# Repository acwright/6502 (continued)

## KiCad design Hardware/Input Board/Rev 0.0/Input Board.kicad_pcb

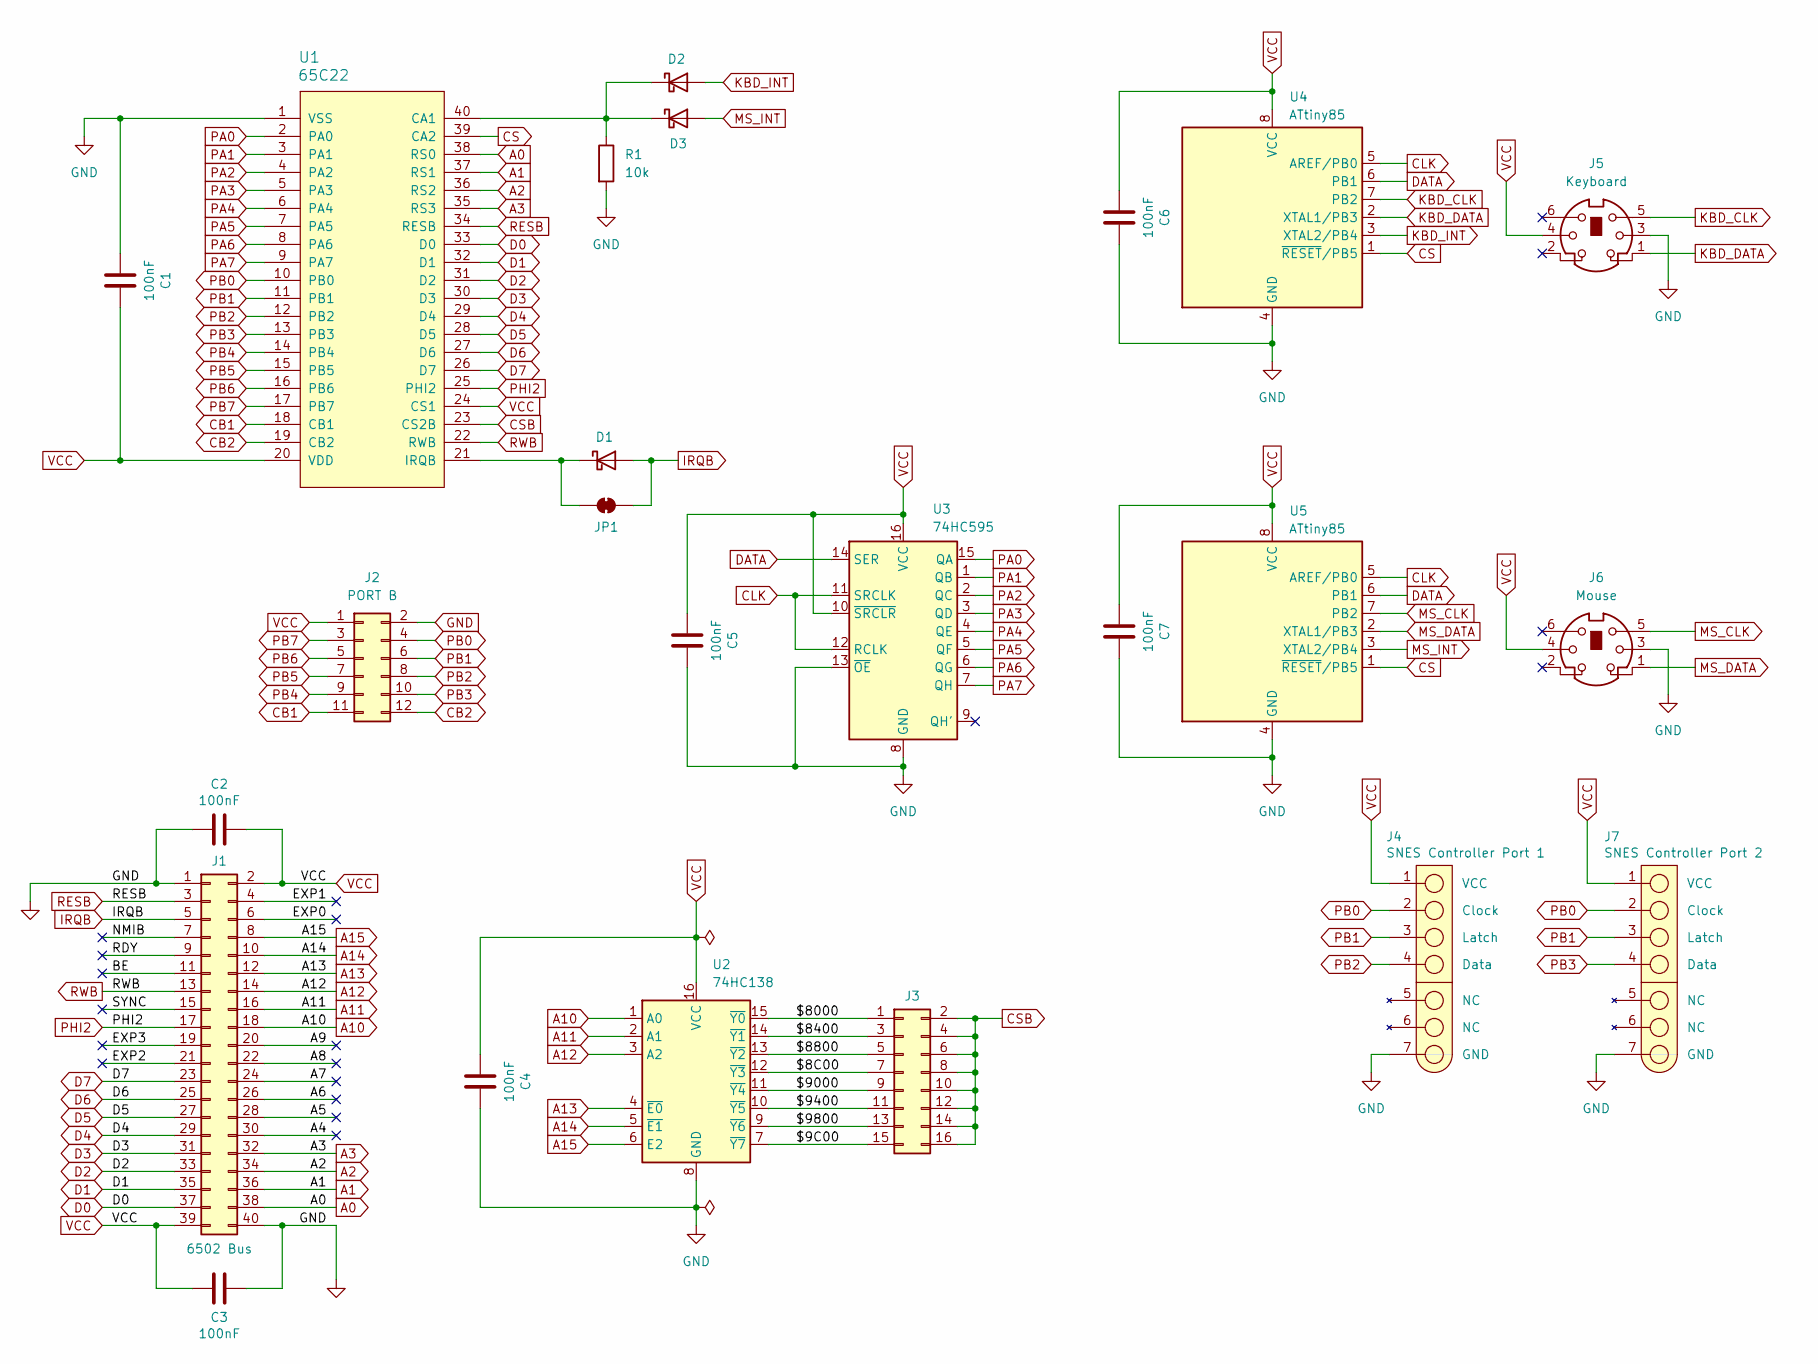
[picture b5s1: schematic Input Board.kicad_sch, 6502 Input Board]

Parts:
C1, C2, C3, C4, C5, C6, C7: 100nF; C_0805_2012Metric; LCSC C49678
D1, D2, D3: D_Schottky; D_DO-35_SOD27_P7.62mm_Horizontal
J1: 6502 Bus; 6502 Bus Connector
J2: PORT B; 6502 GPIO Connector
J3: Conn_02x08_Odd_Even; PinHeader_2x08_P2.54mm_Vertical
J4: SNES Controller Port 1; SNES Controller Port
J5: Keyboard; KMDGX-6S-BS
J6: Mouse; KMDGX-6S-BS
J7: SNES Controller Port 2; SNES Controller Port
JP1: SolderJumper_2_Bridged; SolderJumper-2_P1.3mm_Bridged_RoundedPad1.0x1.5mm
R1: 10k; R_0805_2012Metric; LCSC C17414
U1: 65C22; DIP-40_W15.24mm_Socket_LongPads
U2: 74HC138; SOIC-16_3.9x9.9mm_P1.27mm; LCSC C5602
U3: 74HC595; SOIC-16_3.9x9.9mm_P1.27mm; LCSC C5947
U4, U5: ATtiny85; DIP-8_W7.62mm_Socket_LongPads

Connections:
/$8C00: J3.7, U2.12 (~Y3)
/$9C00: J3.15, U2.7 (~Y7)
/$8000: J3.1, U2.15 (~Y0)
/$8400: J3.3, U2.14 (~Y1)
/$8800: J3.5, U2.13 (~Y2)
/$9000: J3.9, U2.11 (~Y4)
/$9400: J3.11, U2.10 (~Y5)
/$9800: J3.13, U2.9 (~Y6)
/A4: J1.30
/A5: J1.28
/A6: J1.26
/A7: J1.24
/A8: J1.22
/A9: J1.20
/BE: J1.11
/EXP0: J1.6
/EXP1: J1.4
/EXP2: J1.21
/EXP3: J1.19
/NMIB: J1.7
/RDY: J1.9
/SYNC: J1.15
A0: J1.38, U1.38 (RS0)
A1: J1.36, U1.37 (RS1)
A2: J1.34, U1.36 (RS2)
A3: J1.32, U1.35 (RS3)
A10: J1.18, U2.1 (A0)
A11: J1.16, U2.2 (A1)
A12: J1.14, U2.3 (A2)
A13: J1.12, U2.4 (~E0)
A14: J1.10, U2.5 (~E1)
A15: J1.8, U2.6 (E2)
CB1: J2.11, U1.18 (CB1)
CB2: J2.12, U1.19 (CB2)
CLK: U3.11 (SRCLK), U3.12 (RCLK), U4.5 (AREF/PB0), U5.5 (AREF/PB0)
CS: U1.39 (CA2), U4.1 (~RESET/PB5), U5.1 (~RESET/PB5)
CSB: J3.2, J3.4, J3.6, J3.8, J3.10, J3.12, J3.14, J3.16, U1.23 (CS2B)
D0: J1.37, U1.33 (D0)
D1: J1.35, U1.32 (D1)
D2: J1.33, U1.31 (D2)
D3: J1.31, U1.30 (D3)
D4: J1.29, U1.29 (D4)
D5: J1.27, U1.28 (D5)
D6: J1.25, U1.27 (D6)
D7: J1.23, U1.26 (D7)
DATA: U3.14 (SER), U4.6 (PB1), U5.6 (PB1)
GND: C1.1, C2.2, C3.1, C4.2, C5.2, C6.2, C7.2, J1.1, J1.40, J2.2, J4.7 (GND), J5.3, J6.3, J7.7 (GND), R1.2, U1.1 (VSS), U2.8 (GND), U3.8 (GND), U3.13 (~OE), U4.4 (GND), U5.4 (GND)
IRQB: D1.2 (A), J1.5, JP1.2 (B)
KBD_CLK: J5.5, U4.7 (PB2)
KBD_DATA: J5.1, U4.2 (XTAL1/PB3)
KBD_INT: D2.2 (A), U4.3 (XTAL2/PB4)
MS_CLK: J6.5, U5.7 (PB2)
MS_DATA: J6.1, U5.2 (XTAL1/PB3)
MS_INT: D3.2 (A), U5.3 (XTAL2/PB4)
unnamed: D1.1 (K), JP1.1 (A), U1.21 (IRQB)
unnamed: D2.1 (K), D3.1 (K), R1.1, U1.40 (CA1)
PA0: U1.2 (PA0), U3.15 (QA)
PA1: U1.3 (PA1), U3.1 (QB)
PA2: U1.4 (PA2), U3.2 (QC)
PA3: U1.5 (PA3), U3.3 (QD)
PA4: U1.6 (PA4), U3.4 (QE)
PA5: U1.7 (PA5), U3.5 (QF)
PA6: U1.8 (PA6), U3.6 (QG)
PA7: U1.9 (PA7), U3.7 (QH)
PB0: J2.4, J4.2 (Clock), J7.2 (Clock), U1.10 (PB0)
PB1: J2.6, J4.3 (Latch), J7.3 (Latch), U1.11 (PB1)
PB2: J2.8, J4.4 (Data), U1.12 (PB2)
PB3: J2.10, J7.4 (Data), U1.13 (PB3)
PB4: J2.9, U1.14 (PB4)
PB5: J2.7, U1.15 (PB5)
PB6: J2.5, U1.16 (PB6)
PB7: J2.3, U1.17 (PB7)
PHI2: J1.17, U1.25 (PHI2)
RESB: J1.3, U1.34 (RESB)
RWB: J1.13, U1.22 (RWB)
VCC: C1.2, C2.1, C3.2, C4.1, C5.1, C6.1, C7.1, J1.2, J1.39, J2.1, J4.1 (VCC), J5.4, J6.4, J7.1 (VCC), U1.20 (VDD), U1.24 (CS1), U2.16 (VCC), U3.10 (~SRCLR), U3.16 (VCC), U4.8 (VCC), U5.8 (VCC)

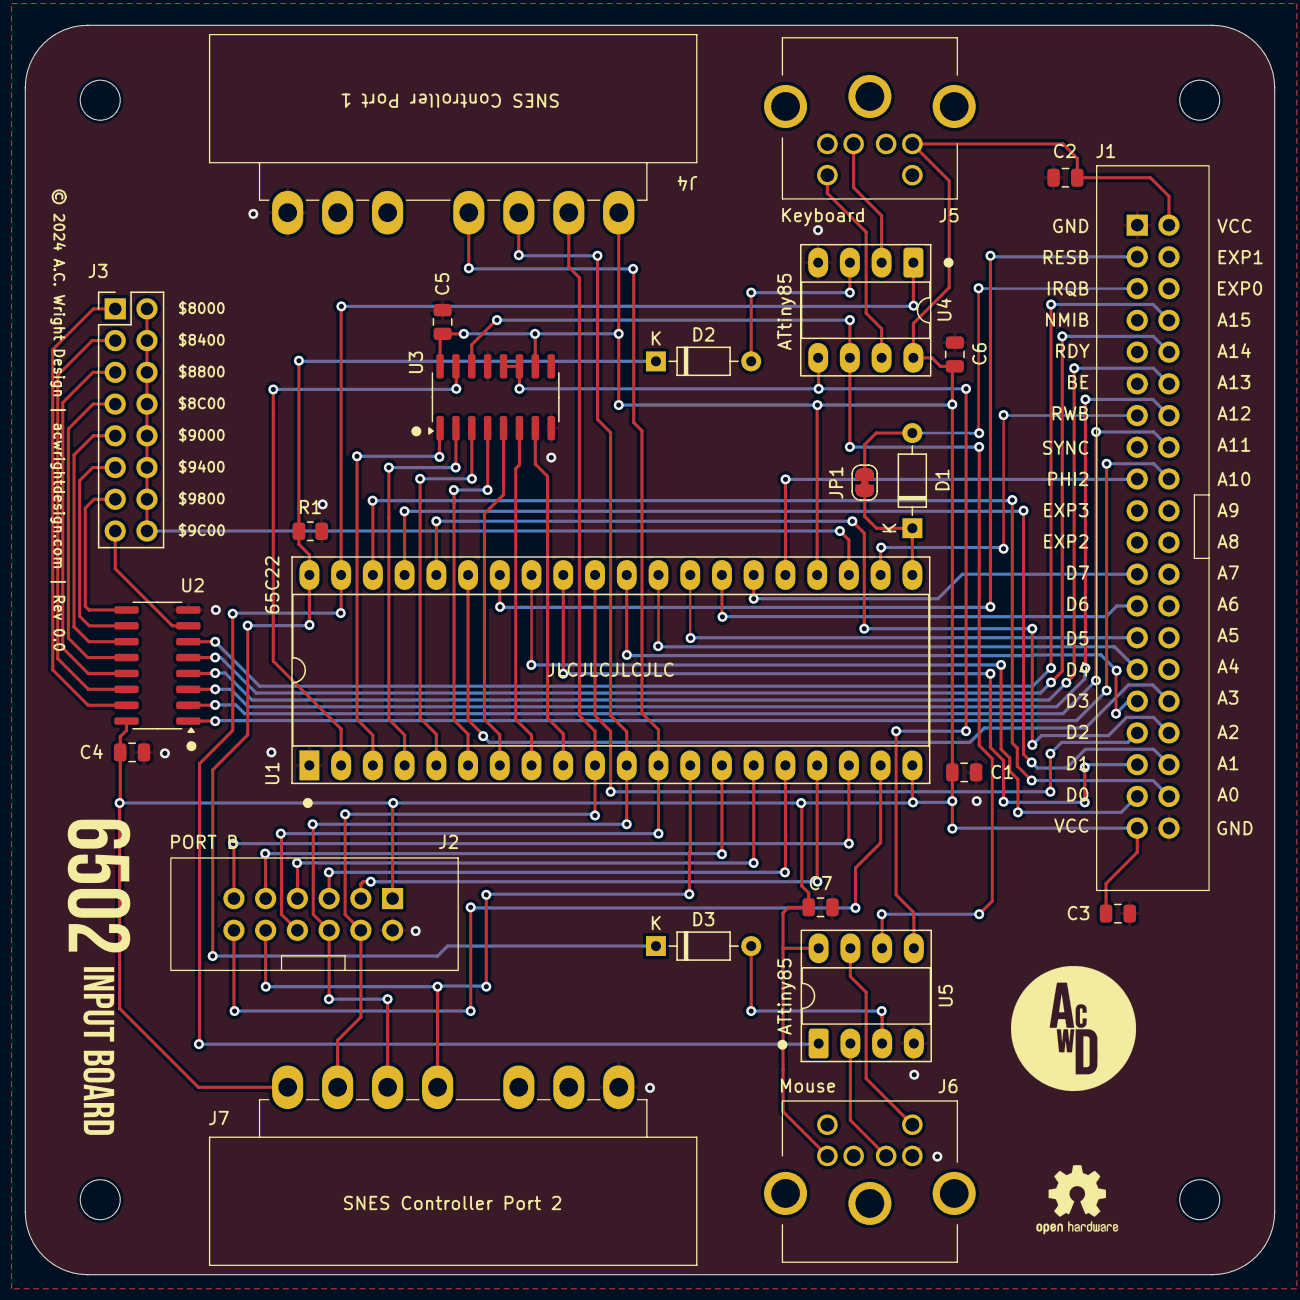
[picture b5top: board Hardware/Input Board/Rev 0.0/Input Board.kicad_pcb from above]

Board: 2 copper layers, 100.0 x 100.0 mm, 28 parts (0 on the bottom side), 62 nets.

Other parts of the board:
H1, H2, H3, H4: MountingHole; MountingHole_3.2mm_M3

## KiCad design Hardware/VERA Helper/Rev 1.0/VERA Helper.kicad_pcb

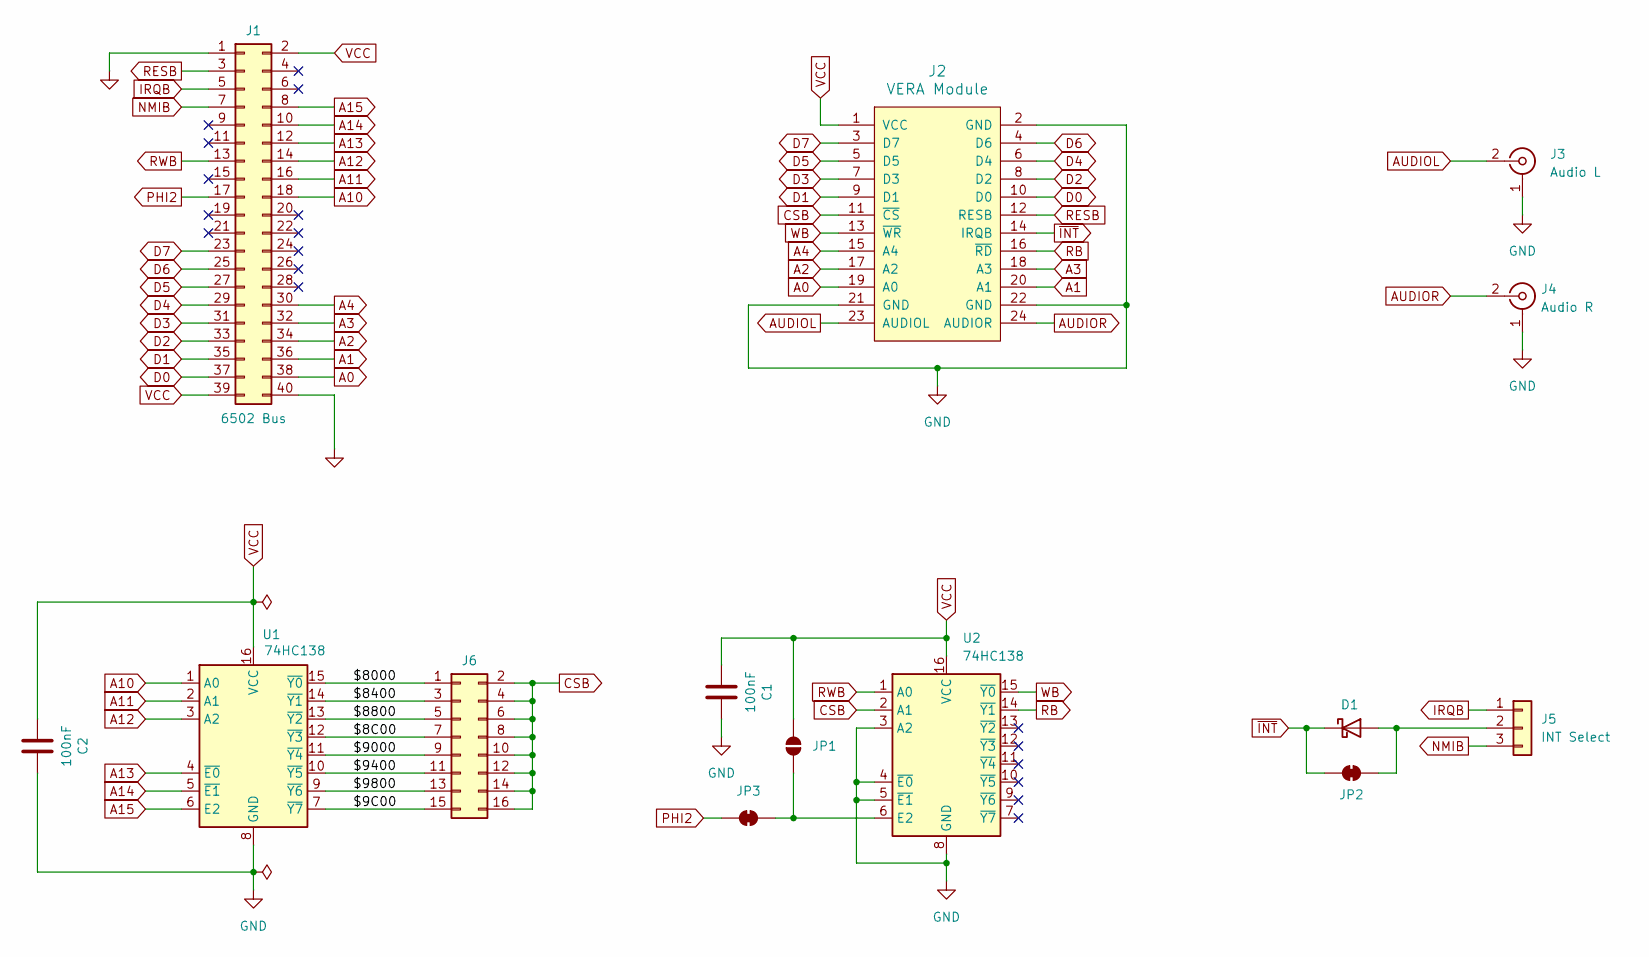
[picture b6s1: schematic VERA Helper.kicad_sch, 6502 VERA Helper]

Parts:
C1, C2: 100nF; C_Disc_D5.0mm_W2.5mm_P5.00mm; LCSC C49678
D1: D_Schottky; D_DO-35_SOD27_P7.62mm_Horizontal
J1: 6502 Bus; 6502 Bus Connector
J2: VERA Module; PinHeader_2x12_P2.54mm_Vertical
J3: Audio L; SWITCHCRAFT_PJRAN1X1U02X
J4: Audio R; SWITCHCRAFT_PJRAN1X1U02X
J5: INT Select; PinHeader_1x03_P2.54mm_Vertical
J6: Conn_02x08_Odd_Even; PinHeader_2x08_P2.54mm_Vertical
JP1: SolderJumper_2_Open; SolderJumper-2_P1.3mm_Open_RoundedPad1.0x1.5mm
JP2, JP3: SolderJumper_2_Bridged; SolderJumper-2_P1.3mm_Bridged_RoundedPad1.0x1.5mm
U1, U2: 74HC138; DIP-16_W7.62mm_Socket_LongPads; LCSC C5602

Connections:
/$8C00: J6.7, U1.12 (~Y3)
/$9C00: J6.15, U1.7 (~Y7)
/$8000: J6.1, U1.15 (~Y0)
/$8400: J6.3, U1.14 (~Y1)
/$8800: J6.5, U1.13 (~Y2)
/$9000: J6.9, U1.11 (~Y4)
/$9400: J6.11, U1.10 (~Y5)
/$9800: J6.13, U1.9 (~Y6)
A0: J1.38, J2.19 (A0)
A1: J1.36, J2.20 (A1)
A2: J1.34, J2.17 (A2)
A3: J1.32, J2.18 (A3)
A4: J1.30, J2.15 (A4)
A10: J1.18, U1.1 (A0)
A11: J1.16, U1.2 (A1)
A12: J1.14, U1.3 (A2)
A13: J1.12, U1.4 (~E0)
A14: J1.10, U1.5 (~E1)
A15: J1.8, U1.6 (E2)
AUDIOL: J2.23 (AUDIOL), J3.2 (In)
AUDIOR: J2.24 (AUDIOR), J4.2 (In)
CSB: J2.11 (~CS), J6.2, J6.4, J6.6, J6.8, J6.10, J6.12, J6.14, J6.16, U2.2 (A1)
D0: J1.37, J2.10 (D0)
D1: J1.35, J2.9 (D1)
D2: J1.33, J2.8 (D2)
D3: J1.31, J2.7 (D3)
D4: J1.29, J2.6 (D4)
D5: J1.27, J2.5 (D5)
D6: J1.25, J2.4 (D6)
D7: J1.23, J2.3 (D7)
GND: C1.2, C2.2, J1.1, J1.40, J2.2 (GND), J2.21 (GND), J2.22 (GND), J3.1 (Ext), J4.1 (Ext), U1.8 (GND), U2.3 (A2), U2.4 (~E0), U2.5 (~E1), U2.8 (GND)
IRQB: J1.5, J5.1
NMIB: J1.7, J5.3
unnamed: D1.2 (A), J5.2, JP2.2 (B)
unnamed: JP1.2 (B), JP3.1 (A), U2.6 (E2)
PHI2: J1.17, JP3.2 (B)
RB: J2.16 (~RD), U2.14 (~Y1)
RESB: J1.3, J2.12 (RESB)
RWB: J1.13, U2.1 (A0)
VCC: C1.1, C2.1, J1.2, J1.39, J2.1 (VCC), JP1.1 (A), U1.16 (VCC), U2.16 (VCC)
WB: J2.13 (~WR), U2.15 (~Y0)
~INT: D1.1 (K), J2.14 (IRQB), JP2.1 (A)

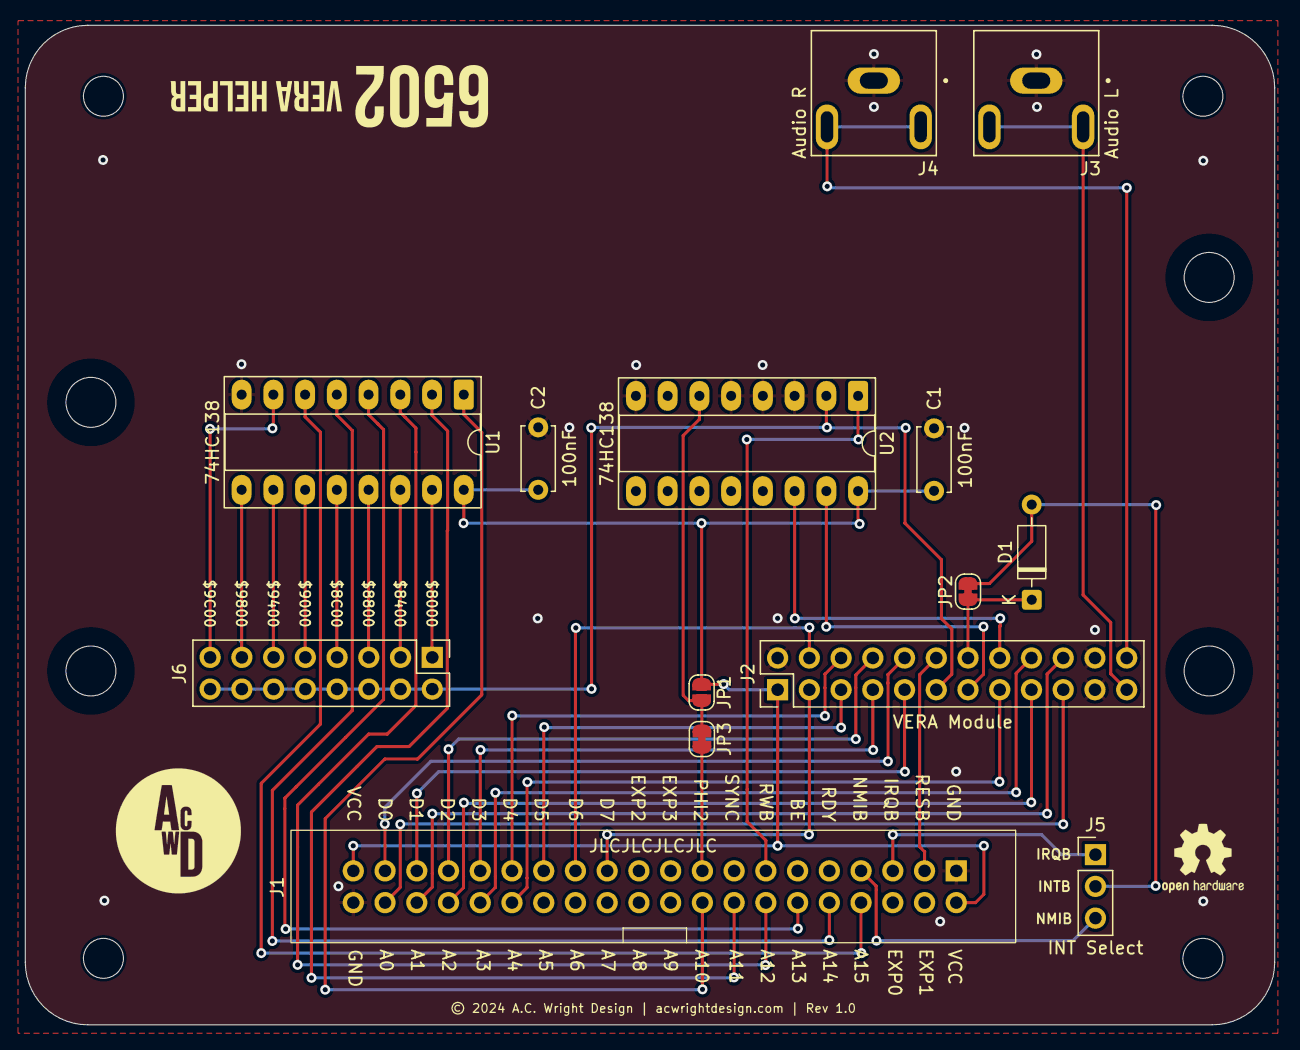
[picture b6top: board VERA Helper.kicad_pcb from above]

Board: 2 copper layers, 100.0 x 80.0 mm, 18 parts (0 on the bottom side), 42 nets.

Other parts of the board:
H1, H2, H3, H4: MountingHole; MountingHole_3.2mm_M3

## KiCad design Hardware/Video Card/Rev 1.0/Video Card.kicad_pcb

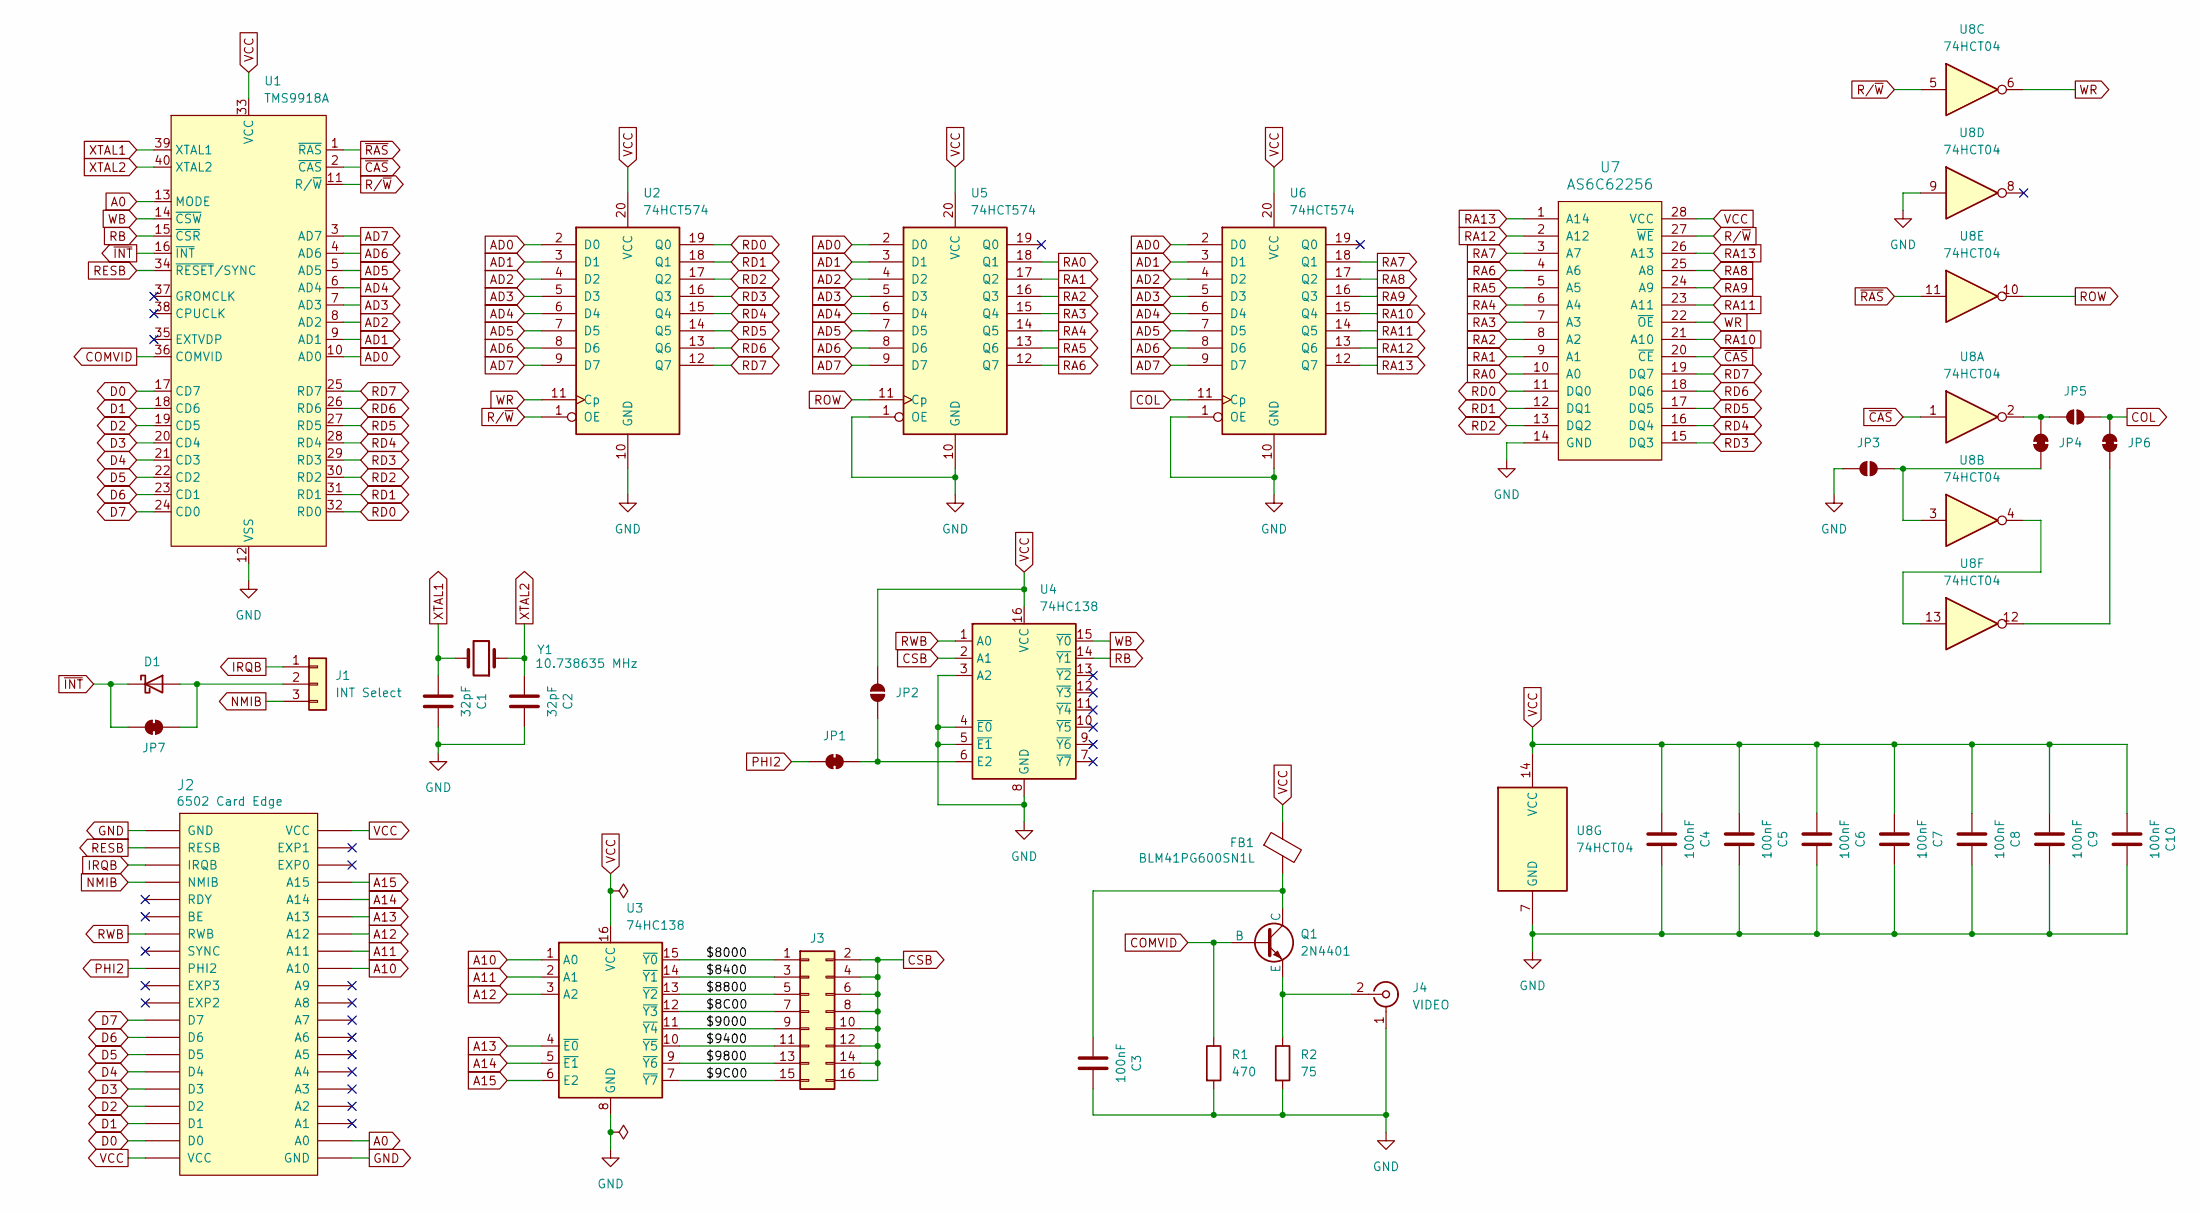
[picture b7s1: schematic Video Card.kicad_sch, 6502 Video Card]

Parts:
C1, C2: 32pF; C_Disc_D5.0mm_W2.5mm_P2.50mm; LCSC C107114
C3, C4, C5, C6, C7, C8, C9, C10: 100nF; C_0805_2012Metric; LCSC C49678
D1: D_Schottky; D_DO-35_SOD27_P7.62mm_Horizontal
FB1: BLM41PG600SN1L; L_1806_4516Metric; LCSC C85844
J1: INT Select; PinHeader_1x03_P2.54mm_Vertical
J2: 6502 Card Edge
J3: Conn_02x08_Odd_Even; PinHeader_2x08_P2.54mm_Vertical
J4: VIDEO; SWITCHCRAFT_PJRAN1X1U04X
JP1, JP4, JP6, JP7: SolderJumper_2_Bridged; SolderJumper-2_P1.3mm_Bridged_RoundedPad1.0x1.5mm
JP2, JP3, JP5: SolderJumper_2_Open; SolderJumper-2_P1.3mm_Open_RoundedPad1.0x1.5mm
Q1: 2N4401; TO-92_HandSolder
R1: 470; R_0805_2012Metric; LCSC C17710
R2: 75; R_0805_2012Metric; LCSC C17820
U1: TMS9918A; DIP-40_W15.24mm_Socket_LongPads
U2, U5, U6: 74HCT574; SOIC-20W_7.5x12.8mm_P1.27mm; LCSC C6001
U3, U4: 74HC138; SOIC-16_3.9x9.9mm_P1.27mm; LCSC C5602
U7: AS6C62256; DIP-28_W15.24mm_Socket_LongPads
U8: 74HCT04; SO-14_3.9x8.65mm_P1.27mm; LCSC C672096
Y1: 10.738635 MHz; Crystal_HC49-U_Vertical; Mouser 774-MP107-E

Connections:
/$8C00: J3.7, U3.12 (~Y3)
/$9C00: J3.15, U3.7 (~Y7)
/$8000: J3.1, U3.15 (~Y0)
/$8400: J3.3, U3.14 (~Y1)
/$8800: J3.5, U3.13 (~Y2)
/$9000: J3.9, U3.11 (~Y4)
/$9400: J3.11, U3.10 (~Y5)
/$9800: J3.13, U3.9 (~Y6)
A0: J2.A0, U1.13 (MODE)
A10: J2.A10, U3.1 (A0)
A11: J2.A11, U3.2 (A1)
A12: J2.A12, U3.3 (A2)
A13: J2.A13, U3.4 (~E0)
A14: J2.A14, U3.5 (~E1)
A15: J2.A15, U3.6 (E2)
AD0: U1.10 (AD0), U2.2 (D0), U5.2 (D0), U6.2 (D0)
AD1: U1.9 (AD1), U2.3 (D1), U5.3 (D1), U6.3 (D1)
AD2: U1.8 (AD2), U2.4 (D2), U5.4 (D2), U6.4 (D2)
AD3: U1.7 (AD3), U2.5 (D3), U5.5 (D3), U6.5 (D3)
AD4: U1.6 (AD4), U2.6 (D4), U5.6 (D4), U6.6 (D4)
AD5: U1.5 (AD5), U2.7 (D5), U5.7 (D5), U6.7 (D5)
AD6: U1.4 (AD6), U2.8 (D6), U5.8 (D6), U6.8 (D6)
AD7: U1.3 (AD7), U2.9 (D7), U5.9 (D7), U6.9 (D7)
COL: JP5.1 (A), JP6.2 (B), U6.11 (Cp)
COMVID: Q1.2 (B), R1.1, U1.36 (COMVID)
CSB: J3.2, J3.4, J3.6, J3.8, J3.10, J3.12, J3.14, J3.16, U4.2 (A1)
D0: J2.D0, U1.17 (CD7)
D1: J2.D1, U1.18 (CD6)
D2: J2.D2, U1.19 (CD5)
D3: J2.D3, U1.20 (CD4)
D4: J2.D4, U1.21 (CD3)
D5: J2.D5, U1.22 (CD2)
D6: J2.D6, U1.23 (CD1)
D7: J2.D7, U1.24 (CD0)
GND: C1.2, C2.2, C3.2, C4.2, C5.2, C6.2, C7.2, C8.2, C9.2, C10.2, J2.GND, J4.1 (Ext), JP3.2 (B), R1.2, R2.2, U1.12 (VSS), U2.10 (GND), U3.8 (GND), U4.3 (A2), U4.4 (~E0), U4.5 (~E1), U4.8 (GND), U5.1 (OE), U5.10 (GND), U6.1 (OE), U6.10 (GND), U7.14 (GND), U8.7 (GND), U8.9
IRQB: J1.1, J2.IRQB
NMIB: J1.3, J2.NMIB
unnamed: D1.2 (A), J1.2, JP7.2 (B)
unnamed: J4.2 (In), Q1.3 (E), R2.1
unnamed: JP1.1 (A), JP2.2 (B), U4.6 (E2)
unnamed: JP3.1 (A), JP4.1 (A), U8.3
unnamed: JP4.2 (B), JP5.2 (B), U8.2
unnamed: JP6.1 (A), U8.12
unnamed: C3.1, FB1.2, Q1.1 (C)
unnamed: U8.4, U8.13
PHI2: J2.PHI2, JP1.2 (B)
RA0: U5.18 (Q1), U7.10 (A0)
RA1: U5.17 (Q2), U7.9 (A1)
RA2: U5.16 (Q3), U7.8 (A2)
RA3: U5.15 (Q4), U7.7 (A3)
RA4: U5.14 (Q5), U7.6 (A4)
RA5: U5.13 (Q6), U7.5 (A5)
RA6: U5.12 (Q7), U7.4 (A6)
RA7: U6.18 (Q1), U7.3 (A7)
RA8: U6.17 (Q2), U7.25 (A8)
RA9: U6.16 (Q3), U7.24 (A9)
RA10: U6.15 (Q4), U7.21 (A10)
RA11: U6.14 (Q5), U7.23 (A11)
RA12: U6.13 (Q6), U7.2 (A12)
RA13: U6.12 (Q7), U7.1 (A14), U7.26 (A13)
RB: U1.15 (~CSR), U4.14 (~Y1)
RD0: U1.32 (RD0), U2.19 (Q0), U7.11 (DQ0)
RD1: U1.31 (RD1), U2.18 (Q1), U7.12 (DQ1)
RD2: U1.30 (RD2), U2.17 (Q2), U7.13 (DQ2)
RD3: U1.29 (RD3), U2.16 (Q3), U7.15 (DQ3)
RD4: U1.28 (RD4), U2.15 (Q4), U7.16 (DQ4)
RD5: U1.27 (RD5), U2.14 (Q5), U7.17 (DQ5)
RD6: U1.26 (RD6), U2.13 (Q6), U7.18 (DQ6)
RD7: U1.25 (RD7), U2.12 (Q7), U7.19 (DQ7)
RESB: J2.RESB, U1.34 (~RESET/SYNC)
ROW: U5.11 (Cp), U8.10
RWB: J2.RWB, U4.1 (A0)
R/~W: U1.11 (R/~W), U2.1 (OE), U7.27 (~WE), U8.5
VCC: C4.1, C5.1, C6.1, C7.1, C8.1, C9.1, C10.1, FB1.1, J2.VCC, JP2.1 (A), U1.33 (VCC), U2.20 (VCC), U3.16 (VCC), U4.16 (VCC), U5.20 (VCC), U6.20 (VCC), U7.28 (VCC), U8.14 (VCC)
WB: U1.14 (~CSW), U4.15 (~Y0)
WR: U2.11 (Cp), U7.22 (~OE), U8.6
XTAL1: C1.1, U1.39 (XTAL1), Y1.2
XTAL2: C2.1, U1.40 (XTAL2), Y1.1
~CAS: U1.2 (~CAS), U7.20 (~CE), U8.1
~INT: D1.1 (K), JP7.1 (A), U1.16 (~INT)
~RAS: U1.1 (~RAS), U8.11

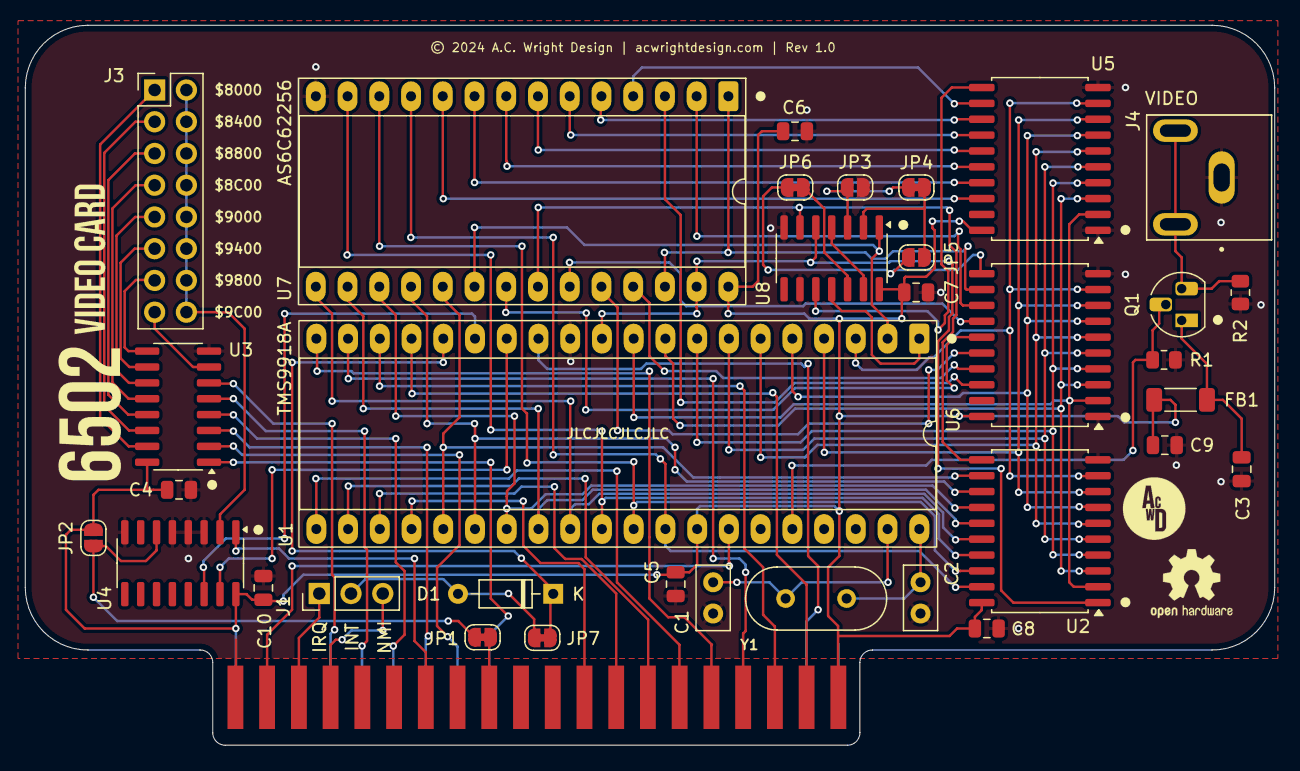
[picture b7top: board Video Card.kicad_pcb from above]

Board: 2 copper layers, 100.0 x 57.6 mm, 35 parts (0 on the bottom side), 81 nets.

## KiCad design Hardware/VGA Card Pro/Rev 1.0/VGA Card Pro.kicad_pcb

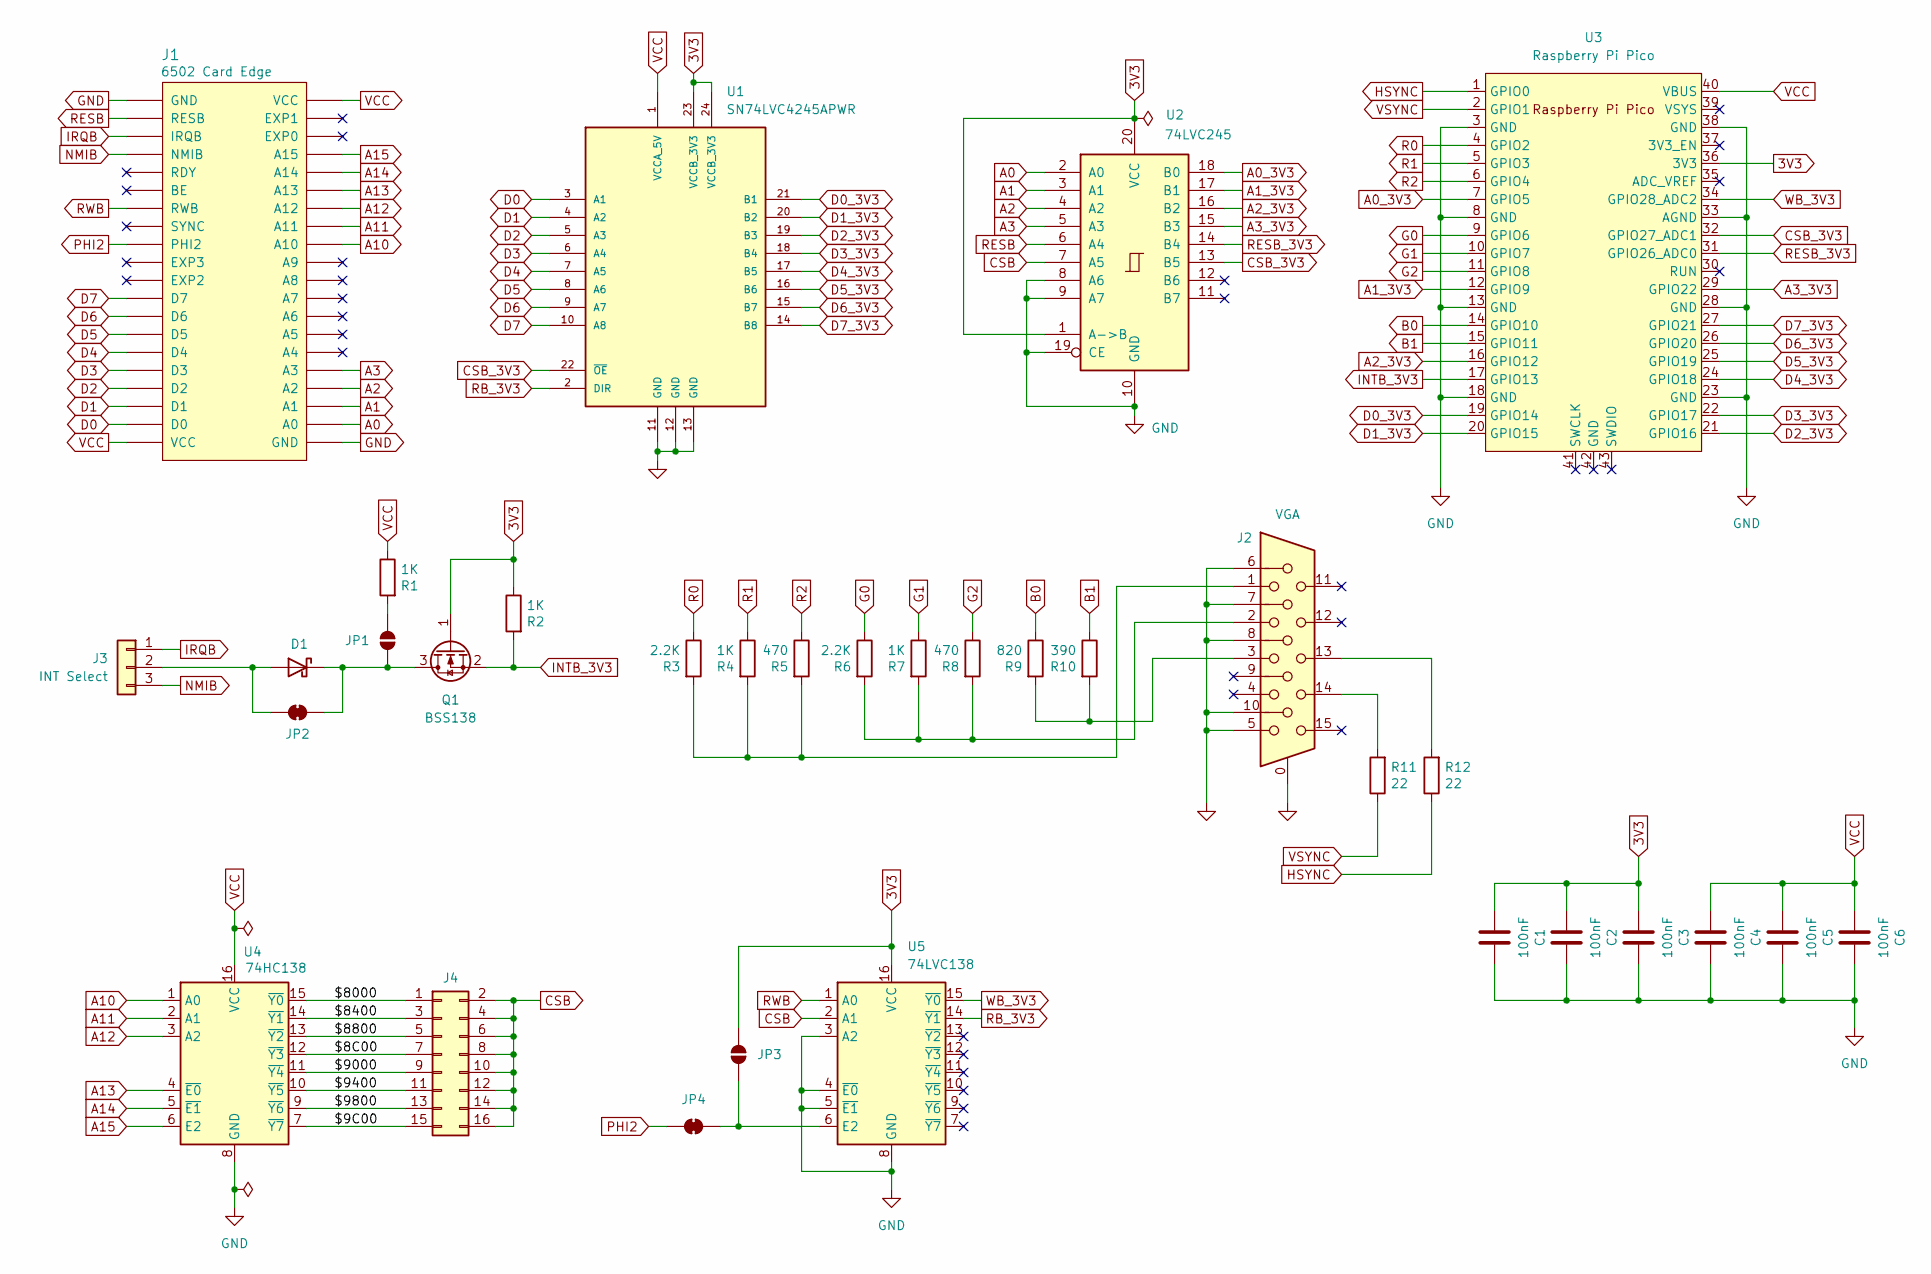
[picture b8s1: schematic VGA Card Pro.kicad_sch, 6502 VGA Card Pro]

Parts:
C1, C2, C3, C4, C5, C6: 100nF; C_0805_2012Metric; LCSC C49678
D1: D_Schottky; D_DO-35_SOD27_P7.62mm_Horizontal
J1: 6502 Card Edge
J2: VGA; DSUB-15-HD_Socket_Horizontal_P2.29x1.90mm_EdgePinOffset3.03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
J3: INT Select; PinHeader_1x03_P2.54mm_Vertical
J4: Conn_02x08_Odd_Even; PinHeader_2x08_P2.54mm_Vertical
JP1, JP3: SolderJumper_2_Open; SolderJumper-2_P1.3mm_Open_RoundedPad1.0x1.5mm
JP2, JP4: SolderJumper_2_Bridged; SolderJumper-2_P1.3mm_Bridged_RoundedPad1.0x1.5mm
Q1: BSS138; SOT-23; LCSC C78284
R1, R2, R4, R7: 1K; R_0805_2012Metric; LCSC C17513
R3, R6: 2.2K; R_0805_2012Metric; LCSC C17520
R5, R8: 470; R_0805_2012Metric; LCSC C17710
R9: 820; R_0805_2012Metric; LCSC C17837
R10: 390; R_0805_2012Metric; LCSC C17655
R11, R12: 22; R_0805_2012Metric; LCSC C17561
U1: SN74LVC4245APWR; TSSOP-24_4.4x7.8mm_P0.65mm; LCSC C7859
U2: 74LVC245; TSSOP-20_4.4x6.5mm_P0.65mm; LCSC C6082
U3: Raspberry Pi Pico
U4: 74HC138; SOIC-16_3.9x9.9mm_P1.27mm; LCSC C5602
U5: 74LVC138; SOIC-16_3.9x9.9mm_P1.27mm; LCSC C6061

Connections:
3V3: C1.1, C2.1, C3.1, JP3.1 (A), Q1.1 (G), R2.1, U1.23 (VCCB_3V3), U1.24 (VCCB_3V3), U2.1 (A->B), U2.20 (VCC), U3.36 (3V3), U5.16 (VCC)
/$8C00: J4.7, U4.12 (~Y3)
/$9C00: J4.15, U4.7 (~Y7)
/$8000: J4.1, U4.15 (~Y0)
/$8400: J4.3, U4.14 (~Y1)
/$8800: J4.5, U4.13 (~Y2)
/$9000: J4.9, U4.11 (~Y4)
/$9400: J4.11, U4.10 (~Y5)
/$9800: J4.13, U4.9 (~Y6)
A0: J1.A0, U2.2 (A0)
A0_3V3: U2.18 (B0), U3.7 (GPIO5)
A1: J1.A1, U2.3 (A1)
A1_3V3: U2.17 (B1), U3.12 (GPIO9)
A2: J1.A2, U2.4 (A2)
A2_3V3: U2.16 (B2), U3.16 (GPIO12)
A3: J1.A3, U2.5 (A3)
A3_3V3: U2.15 (B3), U3.29 (GPIO22)
A10: J1.A10, U4.1 (A0)
A11: J1.A11, U4.2 (A1)
A12: J1.A12, U4.3 (A2)
A13: J1.A13, U4.4 (~E0)
A14: J1.A14, U4.5 (~E1)
A15: J1.A15, U4.6 (E2)
B0: R9.1, U3.14 (GPIO10)
B1: R10.1, U3.15 (GPIO11)
CSB: J4.2, J4.4, J4.6, J4.8, J4.10, J4.12, J4.14, J4.16, U2.7 (A5), U5.2 (A1)
CSB_3V3: U1.22 (~OE), U2.13 (B5), U3.32 (GPIO27_ADC1)
D0: J1.D0, U1.3 (A1)
D0_3V3: U1.21 (B1), U3.19 (GPIO14)
D1: J1.D1, U1.4 (A2)
D1_3V3: U1.20 (B2), U3.20 (GPIO15)
D2: J1.D2, U1.5 (A3)
D2_3V3: U1.19 (B3), U3.21 (GPIO16)
D3: J1.D3, U1.6 (A4)
D3_3V3: U1.18 (B4), U3.22 (GPIO17)
D4: J1.D4, U1.7 (A5)
D4_3V3: U1.17 (B5), U3.24 (GPIO18)
D5: J1.D5, U1.8 (A6)
D5_3V3: U1.16 (B6), U3.25 (GPIO19)
D6: J1.D6, U1.9 (A7)
D6_3V3: U1.15 (B7), U3.26 (GPIO20)
D7: J1.D7, U1.10 (A8)
D7_3V3: U1.14 (B8), U3.27 (GPIO21)
G0: R6.1, U3.9 (GPIO6)
G1: R7.1, U3.10 (GPIO7)
G2: R8.1, U3.11 (GPIO8)
GND: C1.2, C2.2, C3.2, C4.2, C5.2, C6.2, J1.GND, J2.0, J2.5, J2.6, J2.7, J2.8, J2.10, U1.11 (GND), U1.12 (GND), U1.13 (GND), U2.8 (A6), U2.9 (A7), U2.10 (GND), U2.19 (CE), U3.3 (GND), U3.8 (GND), U3.13 (GND), U3.18 (GND), U3.23 (GND), U3.28 (GND), U3.33 (AGND), U3.38 (GND), U4.8 (GND), U5.3 (A2), U5.4 (~E0), U5.5 (~E1), U5.8 (GND)
HSYNC: R12.1, U3.1 (GPIO0)
INTB_3V3: Q1.2 (S), R2.2, U3.17 (GPIO13)
IRQB: J1.IRQB, J3.1
NMIB: J1.NMIB, J3.3
unnamed: D1.2 (A), J3.2, JP2.2 (B)
unnamed: D1.1 (K), JP1.2 (B), JP2.1 (A), Q1.3 (D)
unnamed: J2.1, R3.2, R4.2, R5.2
unnamed: J2.2, R6.2, R7.2, R8.2
unnamed: J2.3, R9.2, R10.2
unnamed: J2.13, R12.2
unnamed: J2.14, R11.2
unnamed: JP1.1 (A), R1.2
unnamed: JP3.2 (B), JP4.1 (A), U5.6 (E2)
PHI2: J1.PHI2, JP4.2 (B)
R0: R3.1, U3.4 (GPIO2)
R1: R4.1, U3.5 (GPIO3)
R2: R5.1, U3.6 (GPIO4)
RB_3V3: U1.2 (DIR), U5.14 (~Y1)
RESB: J1.RESB, U2.6 (A4)
RESB_3V3: U2.14 (B4), U3.31 (GPIO26_ADC0)
RWB: J1.RWB, U5.1 (A0)
VCC: C4.1, C5.1, C6.1, J1.VCC, R1.1, U1.1 (VCCA_5V), U3.40 (VBUS), U4.16 (VCC)
VSYNC: R11.1, U3.2 (GPIO1)
WB_3V3: U3.34 (GPIO28_ADC2), U5.15 (~Y0)

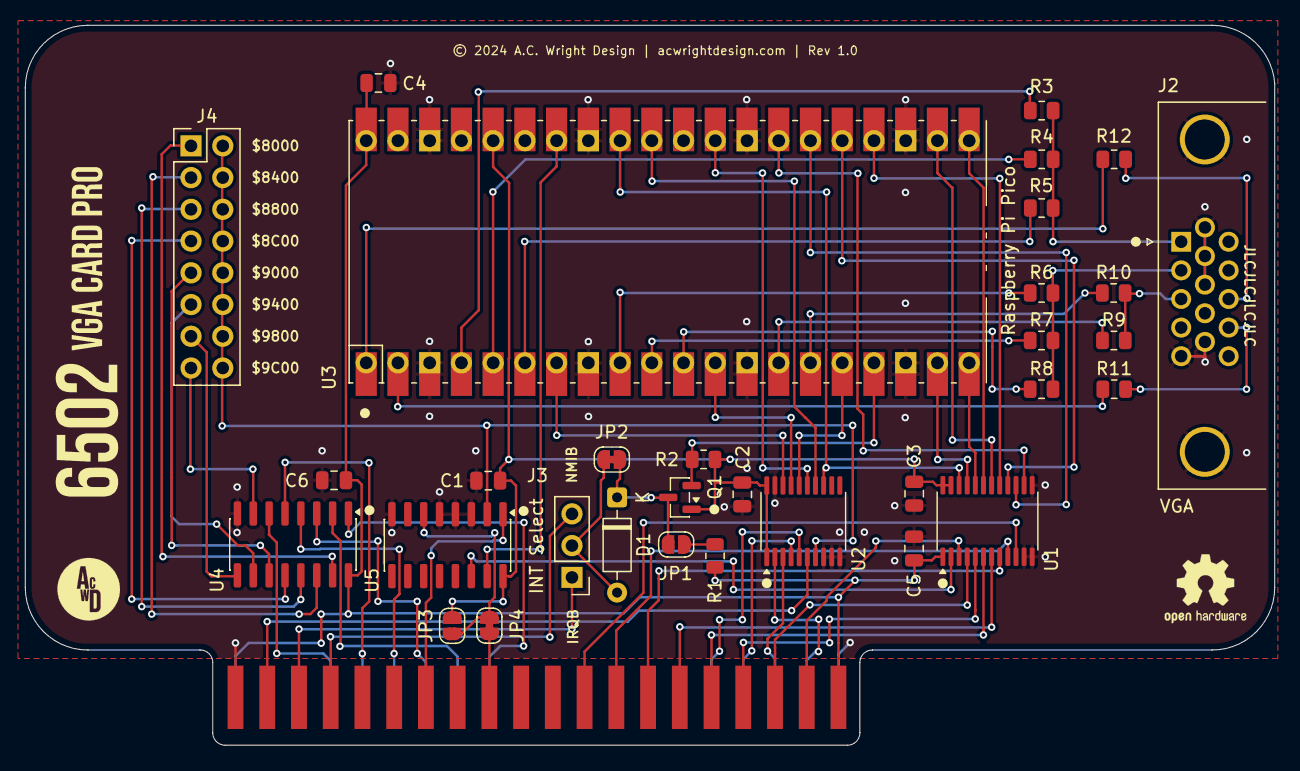
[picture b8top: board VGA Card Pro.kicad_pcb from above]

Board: 2 copper layers, 100.0 x 57.6 mm, 33 parts (0 on the bottom side), 71 nets.
